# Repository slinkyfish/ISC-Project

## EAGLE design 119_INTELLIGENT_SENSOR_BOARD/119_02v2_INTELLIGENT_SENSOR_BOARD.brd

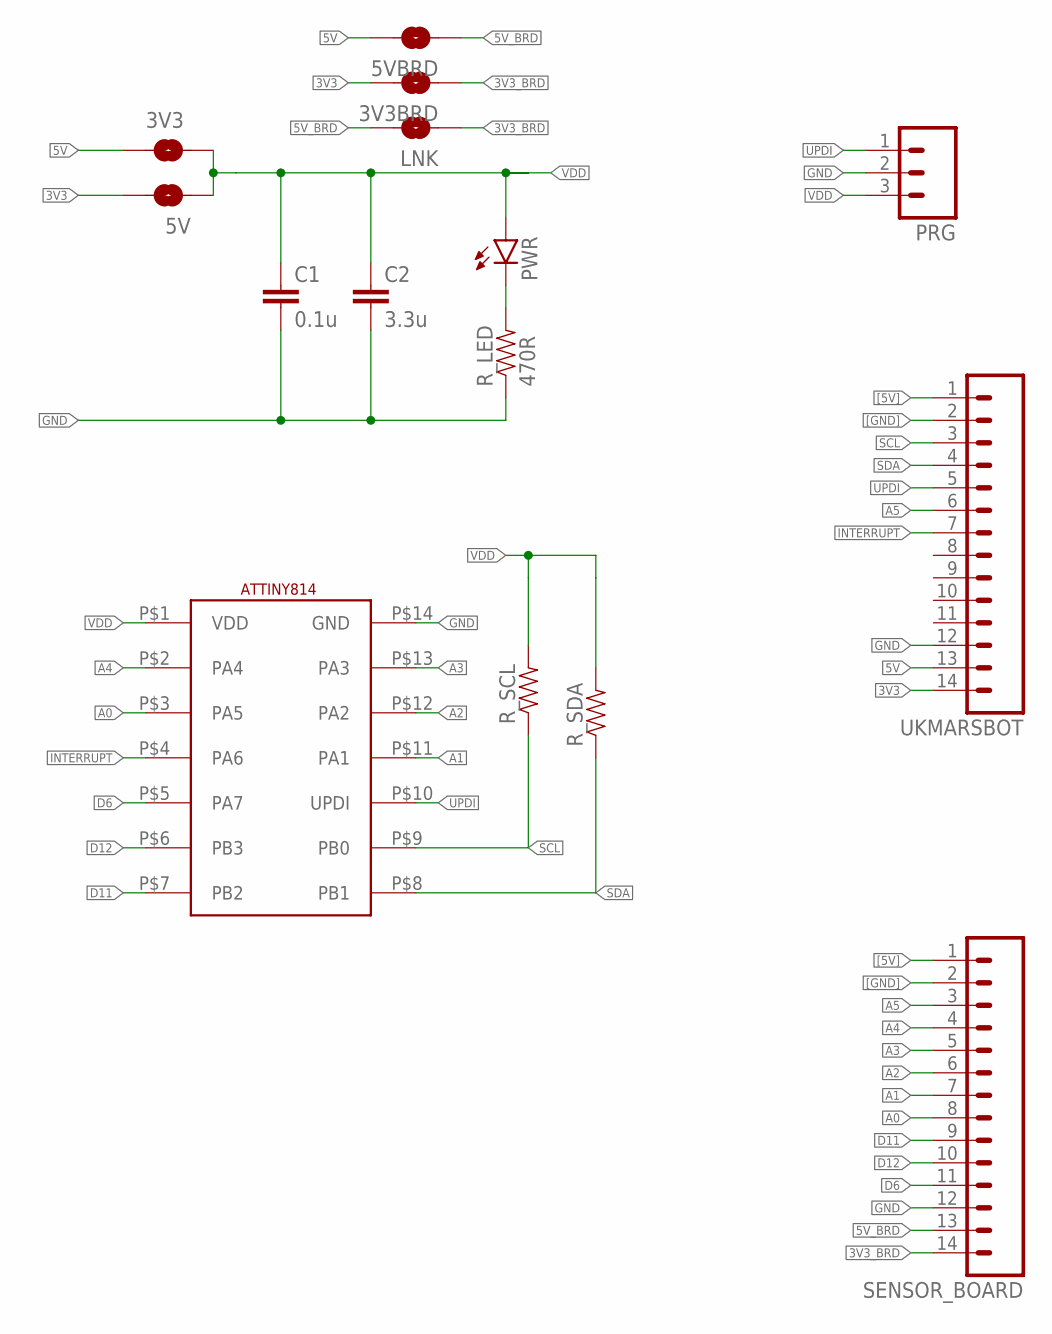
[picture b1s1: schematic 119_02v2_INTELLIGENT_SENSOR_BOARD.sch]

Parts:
3V3, 3V3BRD, 5V, 5VBRD: JUMPER-SMT_2_NO_SILK; SMT-JUMPER_2_NO_SILK
C1: 0.1u; 0805
C2: 3.3u; 0805
LNK: JUMPER-SMT_2_NO_SILK; SMT-JUMPER_2_NO_SILK
PRG: M03PTH; 1X03
PWR: LEDCHIP-LED0805; CHIP-LED0805
R_LED: 470R; 0805
R_SCL: RESISTOR0805-RES; 0805
R_SDA: RESISTOR0805-RES; 0805
SENSOR_BOARD: M14; 1X14
U$1: ATTINY814
UKMARSBOT: M14; 1X14

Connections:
3V3: 3V3BRD.2, 5V.2, UKMARSBOT.14
3V3_BRD: 3V3BRD.1, LNK.1, SENSOR_BOARD.14
5V: 3V3.2, 5VBRD.2, UKMARSBOT.13
5V_BRD: 5VBRD.1, LNK.2, SENSOR_BOARD.13
A0: SENSOR_BOARD.8, U$1.P$3 (PA5)
A1: SENSOR_BOARD.7, U$1.P$11 (PA1)
A2: SENSOR_BOARD.6, U$1.P$12 (PA2)
A3: SENSOR_BOARD.5, U$1.P$13 (PA3)
A4: SENSOR_BOARD.4, U$1.P$2 (PA4)
A5: SENSOR_BOARD.3, UKMARSBOT.6
D6: SENSOR_BOARD.11, U$1.P$5 (PA7)
D11: SENSOR_BOARD.9, U$1.P$7 (PB2)
D12: SENSOR_BOARD.10, U$1.P$6 (PB3)
GND: C1.2, C2.2, PRG.2, R_LED.1, SENSOR_BOARD.12, U$1.P$14 (GND), UKMARSBOT.12
INTERRUPT: U$1.P$4 (PA6), UKMARSBOT.7
unnamed: PWR.C, R_LED.2
SCL: R_SCL.1, U$1.P$9 (PB0), UKMARSBOT.3
SDA: R_SDA.1, U$1.P$8 (PB1), UKMARSBOT.4
UPDI: PRG.1, U$1.P$10 (UPDI), UKMARSBOT.5
VDD: 3V3.1, 5V.1, C1.1, C2.1, PRG.3, PWR.A, R_SCL.2, R_SDA.2, U$1.P$1 (VDD)
[5V]: SENSOR_BOARD.1, UKMARSBOT.1
[GND]: SENSOR_BOARD.2, UKMARSBOT.2

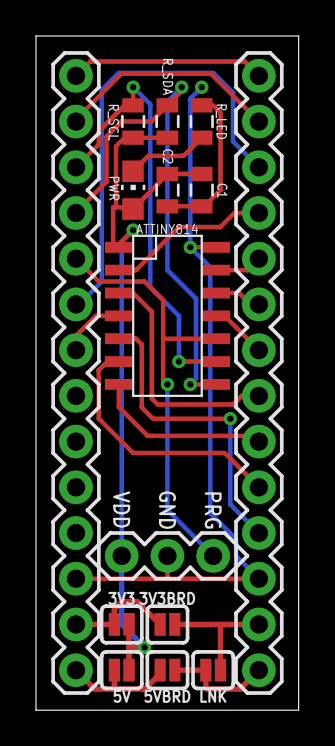
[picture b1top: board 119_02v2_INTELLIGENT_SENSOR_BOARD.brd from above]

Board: 2 copper layers, 14.6 x 37.5 mm, 15 parts (0 on the bottom side), 22 nets.

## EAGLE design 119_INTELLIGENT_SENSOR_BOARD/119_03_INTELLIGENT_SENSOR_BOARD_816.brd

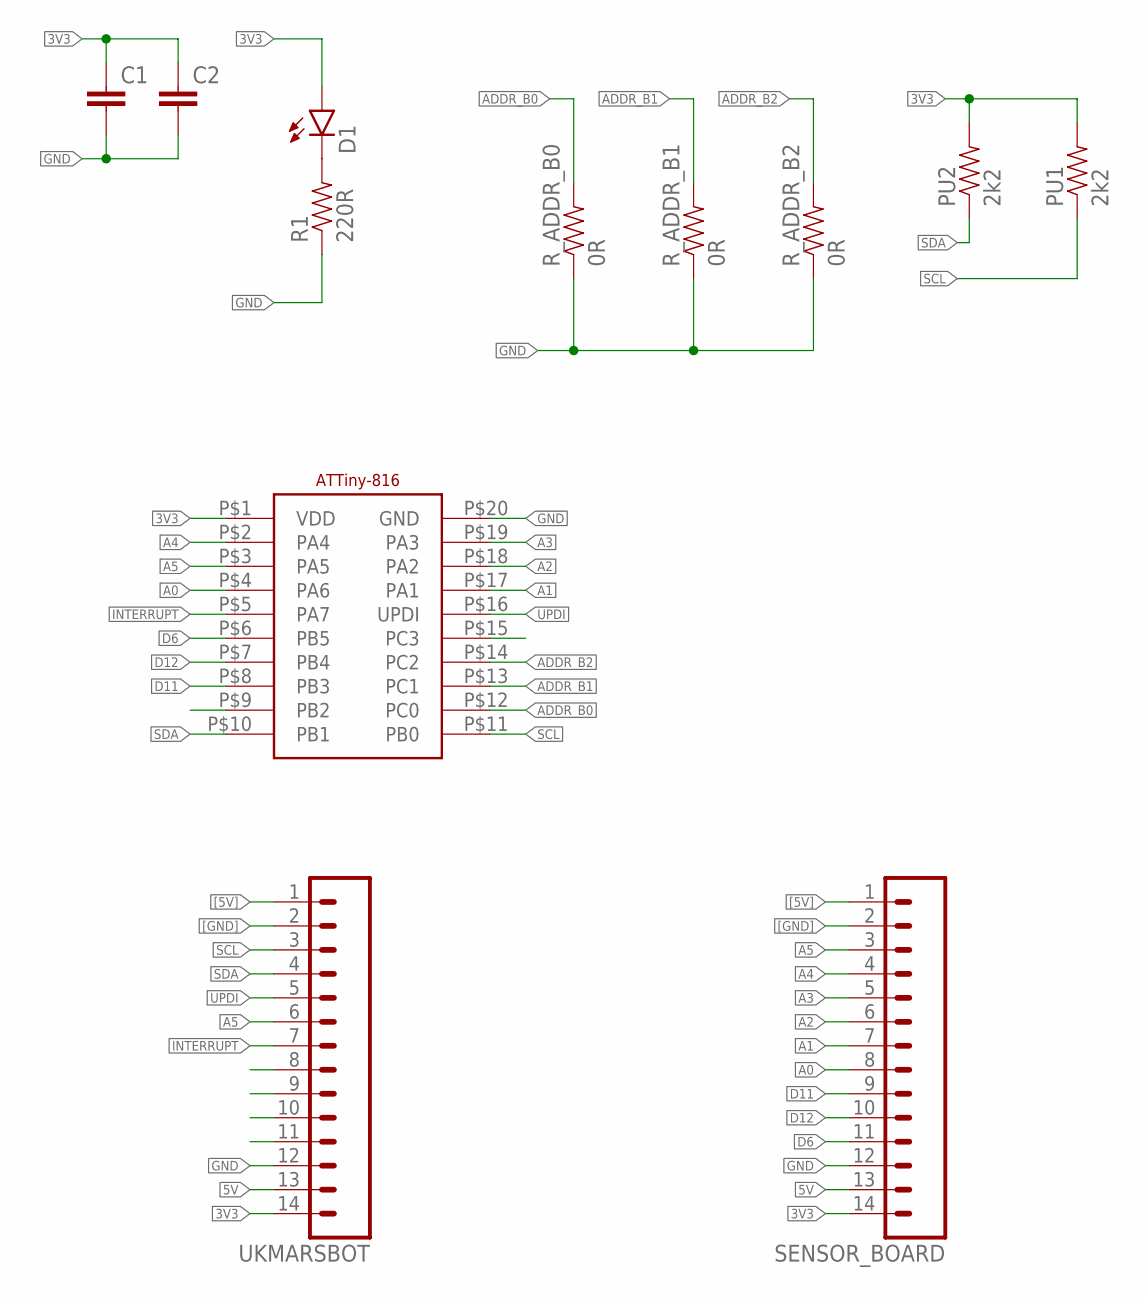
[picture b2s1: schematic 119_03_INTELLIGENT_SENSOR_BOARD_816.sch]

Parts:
C1, C2: CAP0805; 0805
D1: LEDCHIP-LED0805; CHIP-LED0805
PU1, PU2: 2k2; 0805
R1: 220R; 0805
R_ADDR_B0, R_ADDR_B1, R_ADDR_B2: 0R; 0805
SENSOR_BOARD: M14; 14P
U$2: ATTINY816; ATTINY816_SOIC20
UKMARSBOT: M14; 14P

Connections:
3V3: C1.1, C2.1, D1.A, PU1.2, PU2.2, SENSOR_BOARD.14, U$2.P$1 (VDD), UKMARSBOT.14
5V: SENSOR_BOARD.13, UKMARSBOT.13
A0: SENSOR_BOARD.8, U$2.P$4 (PA6)
A1: SENSOR_BOARD.7, U$2.P$17 (PA1)
A2: SENSOR_BOARD.6, U$2.P$18 (PA2)
A3: SENSOR_BOARD.5, U$2.P$19 (PA3)
A4: SENSOR_BOARD.4, U$2.P$2 (PA4)
A5: SENSOR_BOARD.3, U$2.P$3 (PA5), UKMARSBOT.6
ADDR_B0: R_ADDR_B0.2, U$2.P$12 (PC0)
ADDR_B1: R_ADDR_B1.2, U$2.P$13 (PC1)
ADDR_B2: R_ADDR_B2.2, U$2.P$14 (PC2)
D6: SENSOR_BOARD.11, U$2.P$6 (PB5)
D11: SENSOR_BOARD.9, U$2.P$8 (PB3)
D12: SENSOR_BOARD.10, U$2.P$7 (PB4)
GND: C1.2, C2.2, R1.1, R_ADDR_B0.1, R_ADDR_B1.1, R_ADDR_B2.1, SENSOR_BOARD.12, U$2.P$20 (GND), UKMARSBOT.12
INTERRUPT: U$2.P$5 (PA7), UKMARSBOT.7
unnamed: D1.C, R1.2
SCL: PU1.1, U$2.P$11 (PB0), UKMARSBOT.3
SDA: PU2.1, U$2.P$10 (PB1), UKMARSBOT.4
UPDI: U$2.P$16 (UPDI), UKMARSBOT.5
[5V]: SENSOR_BOARD.1, UKMARSBOT.1
[GND]: SENSOR_BOARD.2, UKMARSBOT.2

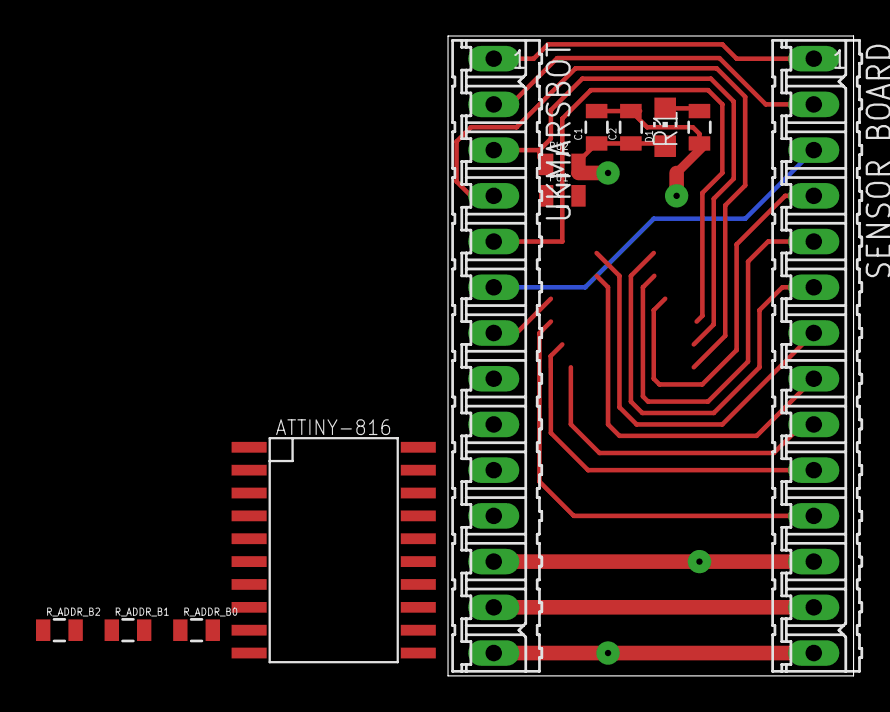
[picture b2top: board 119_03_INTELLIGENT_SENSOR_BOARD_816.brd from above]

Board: 2 copper layers, 22.5 x 35.5 mm, 12 parts (0 on the bottom side), 22 nets.

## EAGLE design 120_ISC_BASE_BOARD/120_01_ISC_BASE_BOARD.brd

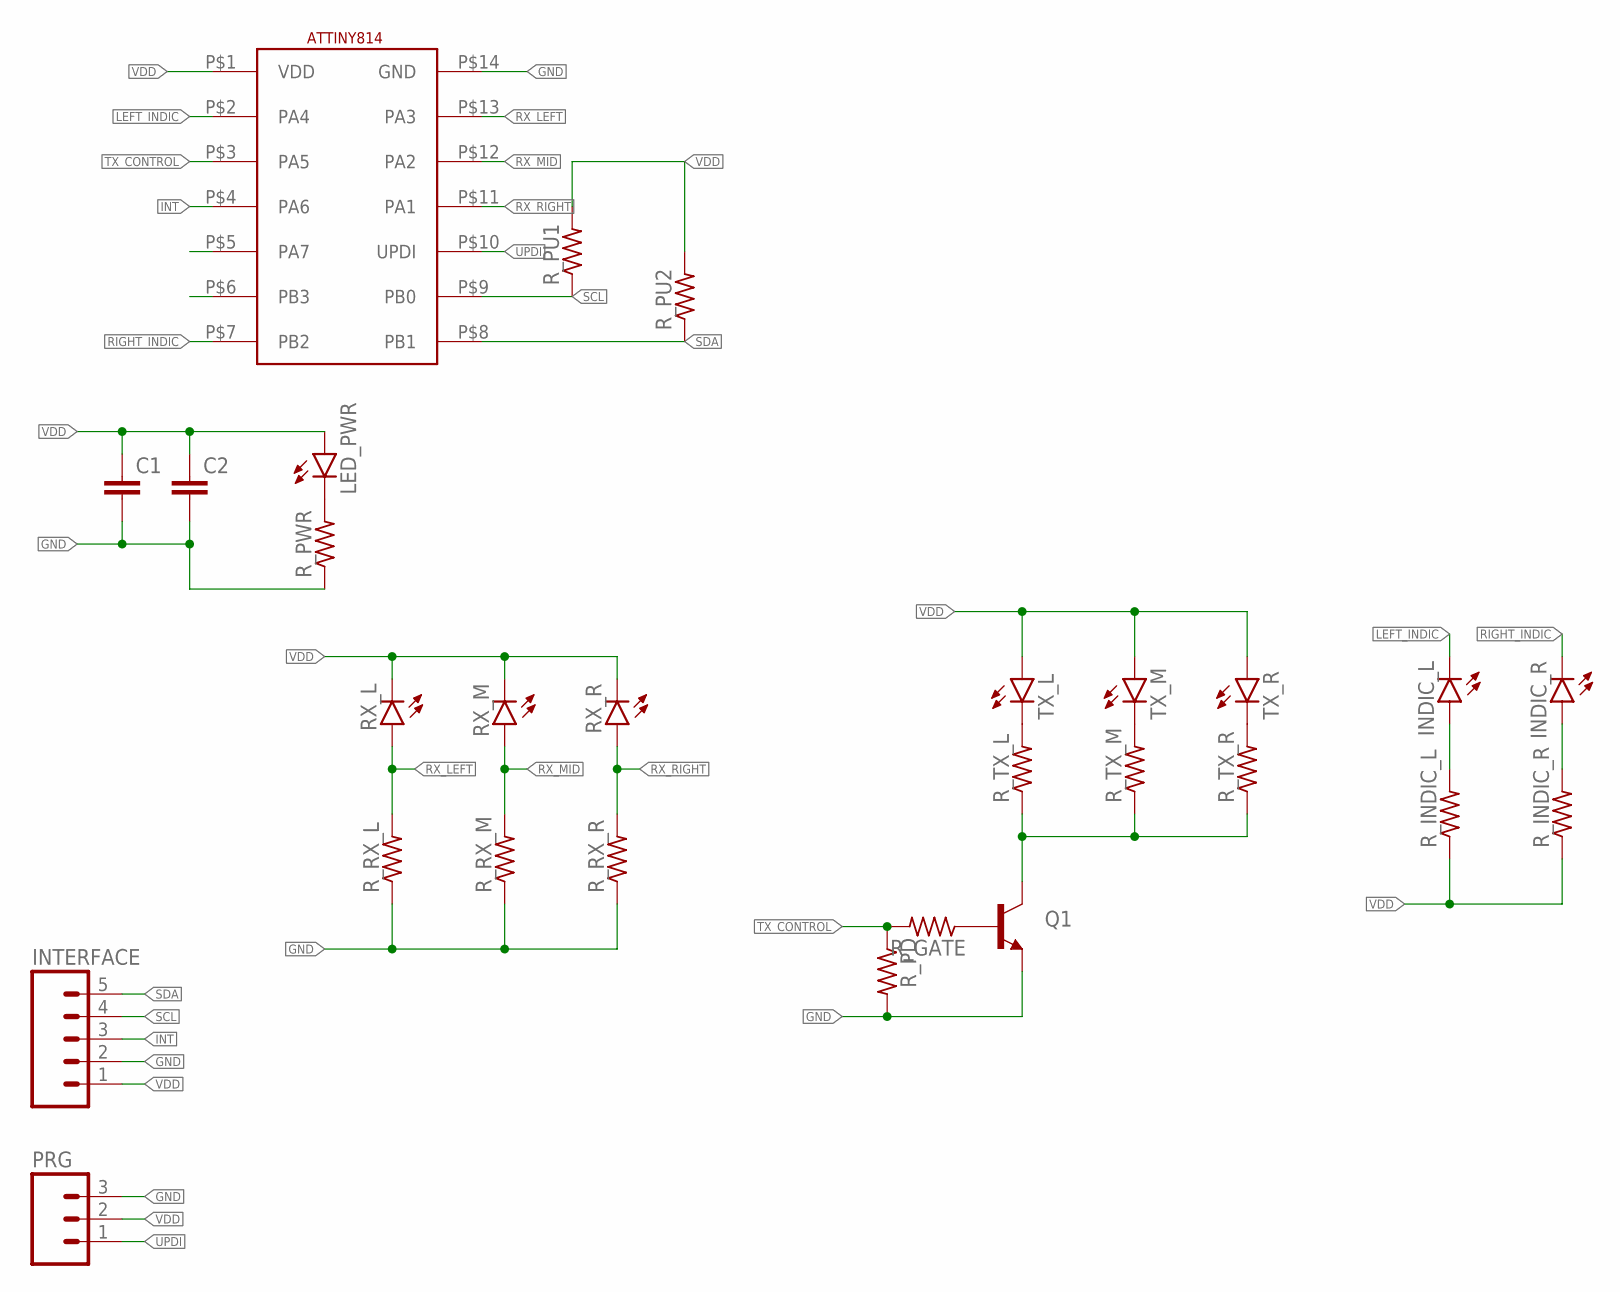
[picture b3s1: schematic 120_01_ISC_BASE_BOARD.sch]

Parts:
C1, C2: C-EUC0805; C0805
INDIC_L: LED3MM
INDIC_R: LED3MM
INTERFACE: M05NO_SILK; 1X05_NO_SILK
LED_PWR: LEDCHIP-LED0805; CHIP-LED0805
PRG: M03PTH; 1X03
Q1: TRANSISTOR_NPNBC547; TO-92-AMMO
RX_L: LED3MM
RX_M: LED3MM
RX_R: LED3MM
R_GATE: R-US_R0805; R0805
R_INDIC_L: R-US_R0805; R0805
R_INDIC_R: R-US_R0805; R0805
R_PD: R-US_R0805; R0805
R_PU1, R_PU2: R-US_R0805; R0805
R_PWR: R-US_R0805; R0805
R_RX_L: R-US_R0805; R0805
R_RX_M: R-US_R0805; R0805
R_RX_R: R-US_R0805; R0805
R_TX_L: R-US_R0805; R0805
R_TX_M: R-US_R0805; R0805
R_TX_R: R-US_R0805; R0805
TX_L: LED5MM
TX_M: LED5MM
TX_R: LED5MM
U$1: ATTINY814

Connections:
GND: C1.2, C2.2, INTERFACE.2, PRG.3, Q1.3 (E), R_PD.2, R_PWR.1, R_RX_L.1, R_RX_M.1, R_RX_R.1, U$1.P$14 (GND)
INT: INTERFACE.3, U$1.P$4 (PA6)
LEFT_INDIC: INDIC_L.K (C), U$1.P$2 (PA4)
unnamed: LED_PWR.C, R_PWR.2
unnamed: INDIC_L.A, R_INDIC_L.2
unnamed: INDIC_R.A, R_INDIC_R.2
unnamed: R_TX_L.2, TX_L.K (C)
unnamed: R_TX_M.2, TX_M.K (C)
unnamed: R_TX_R.2, TX_R.K (C)
unnamed: Q1.1 (C), R_TX_L.1, R_TX_M.1, R_TX_R.1
unnamed: Q1.2 (B), R_GATE.1
RIGHT_INDIC: INDIC_R.K (C), U$1.P$7 (PB2)
RX_LEFT: RX_L.A, R_RX_L.2, U$1.P$13 (PA3)
RX_MID: RX_M.A, R_RX_M.2, U$1.P$12 (PA2)
RX_RIGHT: RX_R.A, R_RX_R.2, U$1.P$11 (PA1)
SCL: INTERFACE.4, R_PU1.1, U$1.P$9 (PB0)
SDA: INTERFACE.5, R_PU2.1, U$1.P$8 (PB1)
TX_CONTROL: R_GATE.2, R_PD.1, U$1.P$3 (PA5)
UPDI: PRG.1, U$1.P$10 (UPDI)
VDD: C1.1, C2.1, INTERFACE.1, LED_PWR.A, PRG.2, RX_L.K (C), RX_M.K (C), RX_R.K (C), R_INDIC_L.1, R_INDIC_R.1, R_PU1.2, R_PU2.2, TX_L.A, TX_M.A, TX_R.A, U$1.P$1 (VDD)

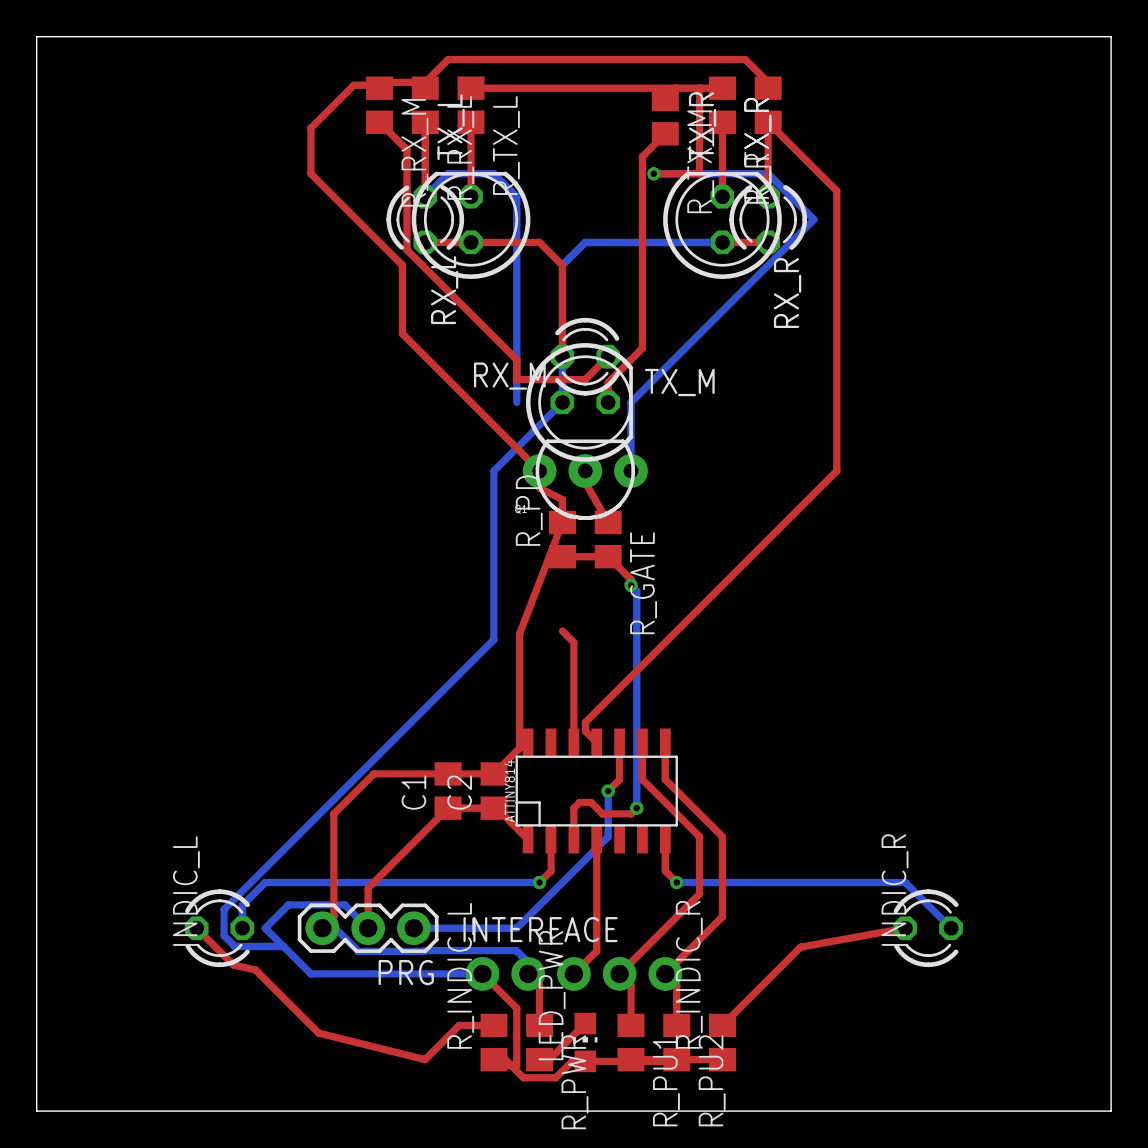
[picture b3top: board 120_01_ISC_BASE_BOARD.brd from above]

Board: 2 copper layers, 59.7 x 59.7 mm, 28 parts (0 on the bottom side), 20 nets.

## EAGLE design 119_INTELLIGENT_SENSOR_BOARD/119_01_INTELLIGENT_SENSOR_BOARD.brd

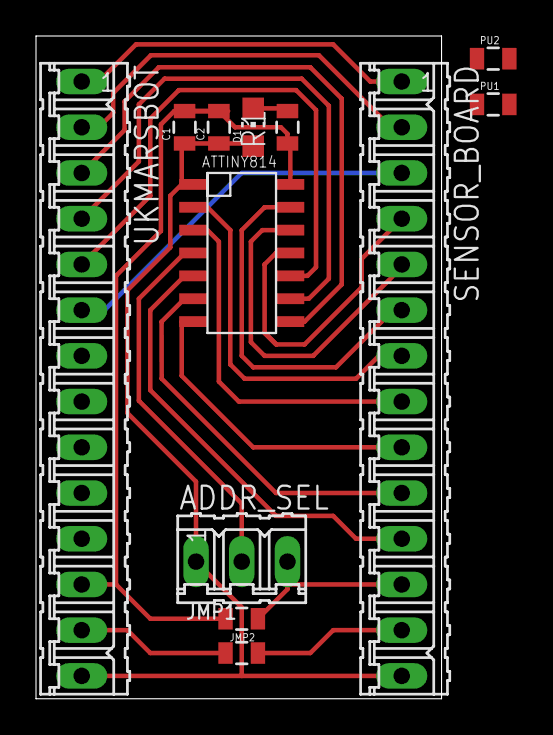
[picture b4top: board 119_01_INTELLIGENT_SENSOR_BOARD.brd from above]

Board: 2 copper layers, 22.5 x 36.8 mm, 12 parts (0 on the bottom side), 19 nets.

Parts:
ADDR_SEL: 03P
C1, C2: 0805
D1: CHIP-LED0805
JMP1, JMP2: 0805
PU1, PU2: 0805
R1: 0805
SENSOR_BOARD: 14P
U$1: ATTINY814
UKMARSBOT: 14P

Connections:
3V3: ADDR_SEL.1, C1.1, C2.1, D1.A, PU1.2, PU2.2, SENSOR_BOARD.14, U$1.P$1, UKMARSBOT.14
5V: JMP1.1, JMP1.2, SENSOR_BOARD.13, UKMARSBOT.13
A0: SENSOR_BOARD.8, U$1.P$3
A1: SENSOR_BOARD.7, U$1.P$2
A2: SENSOR_BOARD.6, U$1.P$13
A3: SENSOR_BOARD.5, U$1.P$12
A4: SENSOR_BOARD.4, U$1.P$11
A5: SENSOR_BOARD.3, UKMARSBOT.6
ADDR_BIT: ADDR_SEL.2, U$1.P$4
D6: SENSOR_BOARD.11, U$1.P$5
D11: SENSOR_BOARD.9, U$1.P$7
D12: SENSOR_BOARD.10, U$1.P$6
GND: ADDR_SEL.3, C1.2, C2.2, JMP2.1, JMP2.2, R1.1, SENSOR_BOARD.12, U$1.P$14, UKMARSBOT.12
unnamed: D1.C, R1.2
SCL: PU1.1, U$1.P$8, UKMARSBOT.3
SDA: PU2.1, U$1.P$9, UKMARSBOT.4
UPDI: U$1.P$10, UKMARSBOT.5
[5V]: SENSOR_BOARD.1, UKMARSBOT.1
[GND]: SENSOR_BOARD.2, UKMARSBOT.2

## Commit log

2021-02-10 Added PCB designs
2021-02-11 Formed new documentation
    Split manual into datasheet, library and notes... added a few more ISC library header defines
2021-04-04 modified
2021-04-04 Works up to and including Ex4
2021-04-05 Published Version 1
2021-04-05 Release V1
2021-06-12 new version

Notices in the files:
parts and their libraries:
SparkFun-Capacitors: Licensing: Creative Commons ShareAlike 4.0 International - https://creativecommons.org/licenses/by-sa/4.0
